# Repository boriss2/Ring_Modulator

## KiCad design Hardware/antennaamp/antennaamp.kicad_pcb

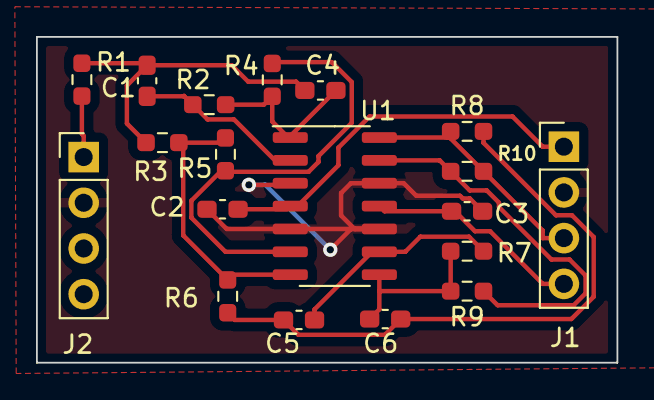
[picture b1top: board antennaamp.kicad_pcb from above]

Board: 2 copper layers, 32.2 x 18.1 mm, 19 parts (0 on the bottom side), 14 nets.

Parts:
C1, C4, C5, C6: 220pF; C_0603_1608Metric_Pad1.08x0.95mm_HandSolder
C2: 100nf; C_0603_1608Metric_Pad1.08x0.95mm_HandSolder
C3: 100nF; C_0603_1608Metric_Pad1.08x0.95mm_HandSolder
J1: PoweIn; PinHeader_1x04_P2.54mm_Vertical
J2: Antenna; PinHeader_1x04_P2.54mm_Vertical
R1, R2, R4, R6, R7, R9: 43K; R_0603_1608Metric_Pad0.98x0.95mm_HandSolder
R3, R8: 16k; R_0603_1608Metric_Pad0.98x0.95mm_HandSolder
R5, R10: 30K; R_0603_1608Metric_Pad0.98x0.95mm_HandSolder
U1: TL084; SOIC-14_3.9x8.7mm_P1.27mm

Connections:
+12V: C2.2, J1.1, U1.4 (V+)
-12V: C3.2, J1.4, U1.11 (V-)
GND: C2.1, C3.1, J1.2, J2.2, U1.3 (+), U1.5 (+), U1.10 (+), U1.12 (+)
unnamed: C1.1, R2.2, U1.2 (-)
unnamed: C1.2, C4.2, R1.1, R3.2
unnamed: C4.1, R2.1, R4.2, U1.1
unnamed: C5.1, R7.2, U1.9 (-)
unnamed: C5.2, C6.2, R6.1, R8.2
unnamed: C6.1, R7.1, R9.2, U1.8
unnamed: J1.3, R8.1, R10.1, U1.14
unnamed: J2.1, R1.2
unnamed: R3.1, R5.1, R6.2, U1.7
unnamed: R4.1, R5.2, U1.6 (-)
unnamed: R9.1, R10.2, U1.13 (-)

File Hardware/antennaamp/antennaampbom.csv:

"Id";"Designator";"Package";"Quantity";"Designation";"Supplier and ref";
1;"U1";"SOIC-14_3.9x8.7mm_P1.27mm";1;"TL084";;;
2;"R10,R5";"R_0603_1608Metric_Pad0.98x0.95mm_HandSolder";2;"30K";;;
3;"R9,R7,R6,R4,R2";"R_0603_1608Metric_Pad0.98x0.95mm_HandSolder";5;"43K";;;
4;"R8,R3";"R_0603_1608Metric_Pad0.98x0.95mm_HandSolder";2;"16k";;;
5;"R1";"R_0603_1608Metric";1;"43K";;;
6;"J2,J1";"PinHeader_1x04_P2.54mm_Vertical";2;"PoweIn";;;
7;"C6,C5,C4,C1";"C_0603_1608Metric_Pad1.08x0.95mm_HandSolder";4;"220pF";;;
8;"C3";"C_0603_1608Metric_Pad1.08x0.95mm_HandSolder";1;"100nF";;;
9;"C2";"C_0603_1608Metric_Pad1.08x0.95mm_HandSolder";1;"100nf";;;

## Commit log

2022-04-26 initial check in
2022-04-27 Code Cleanup
2022-05-05 Added Antenna Amp
